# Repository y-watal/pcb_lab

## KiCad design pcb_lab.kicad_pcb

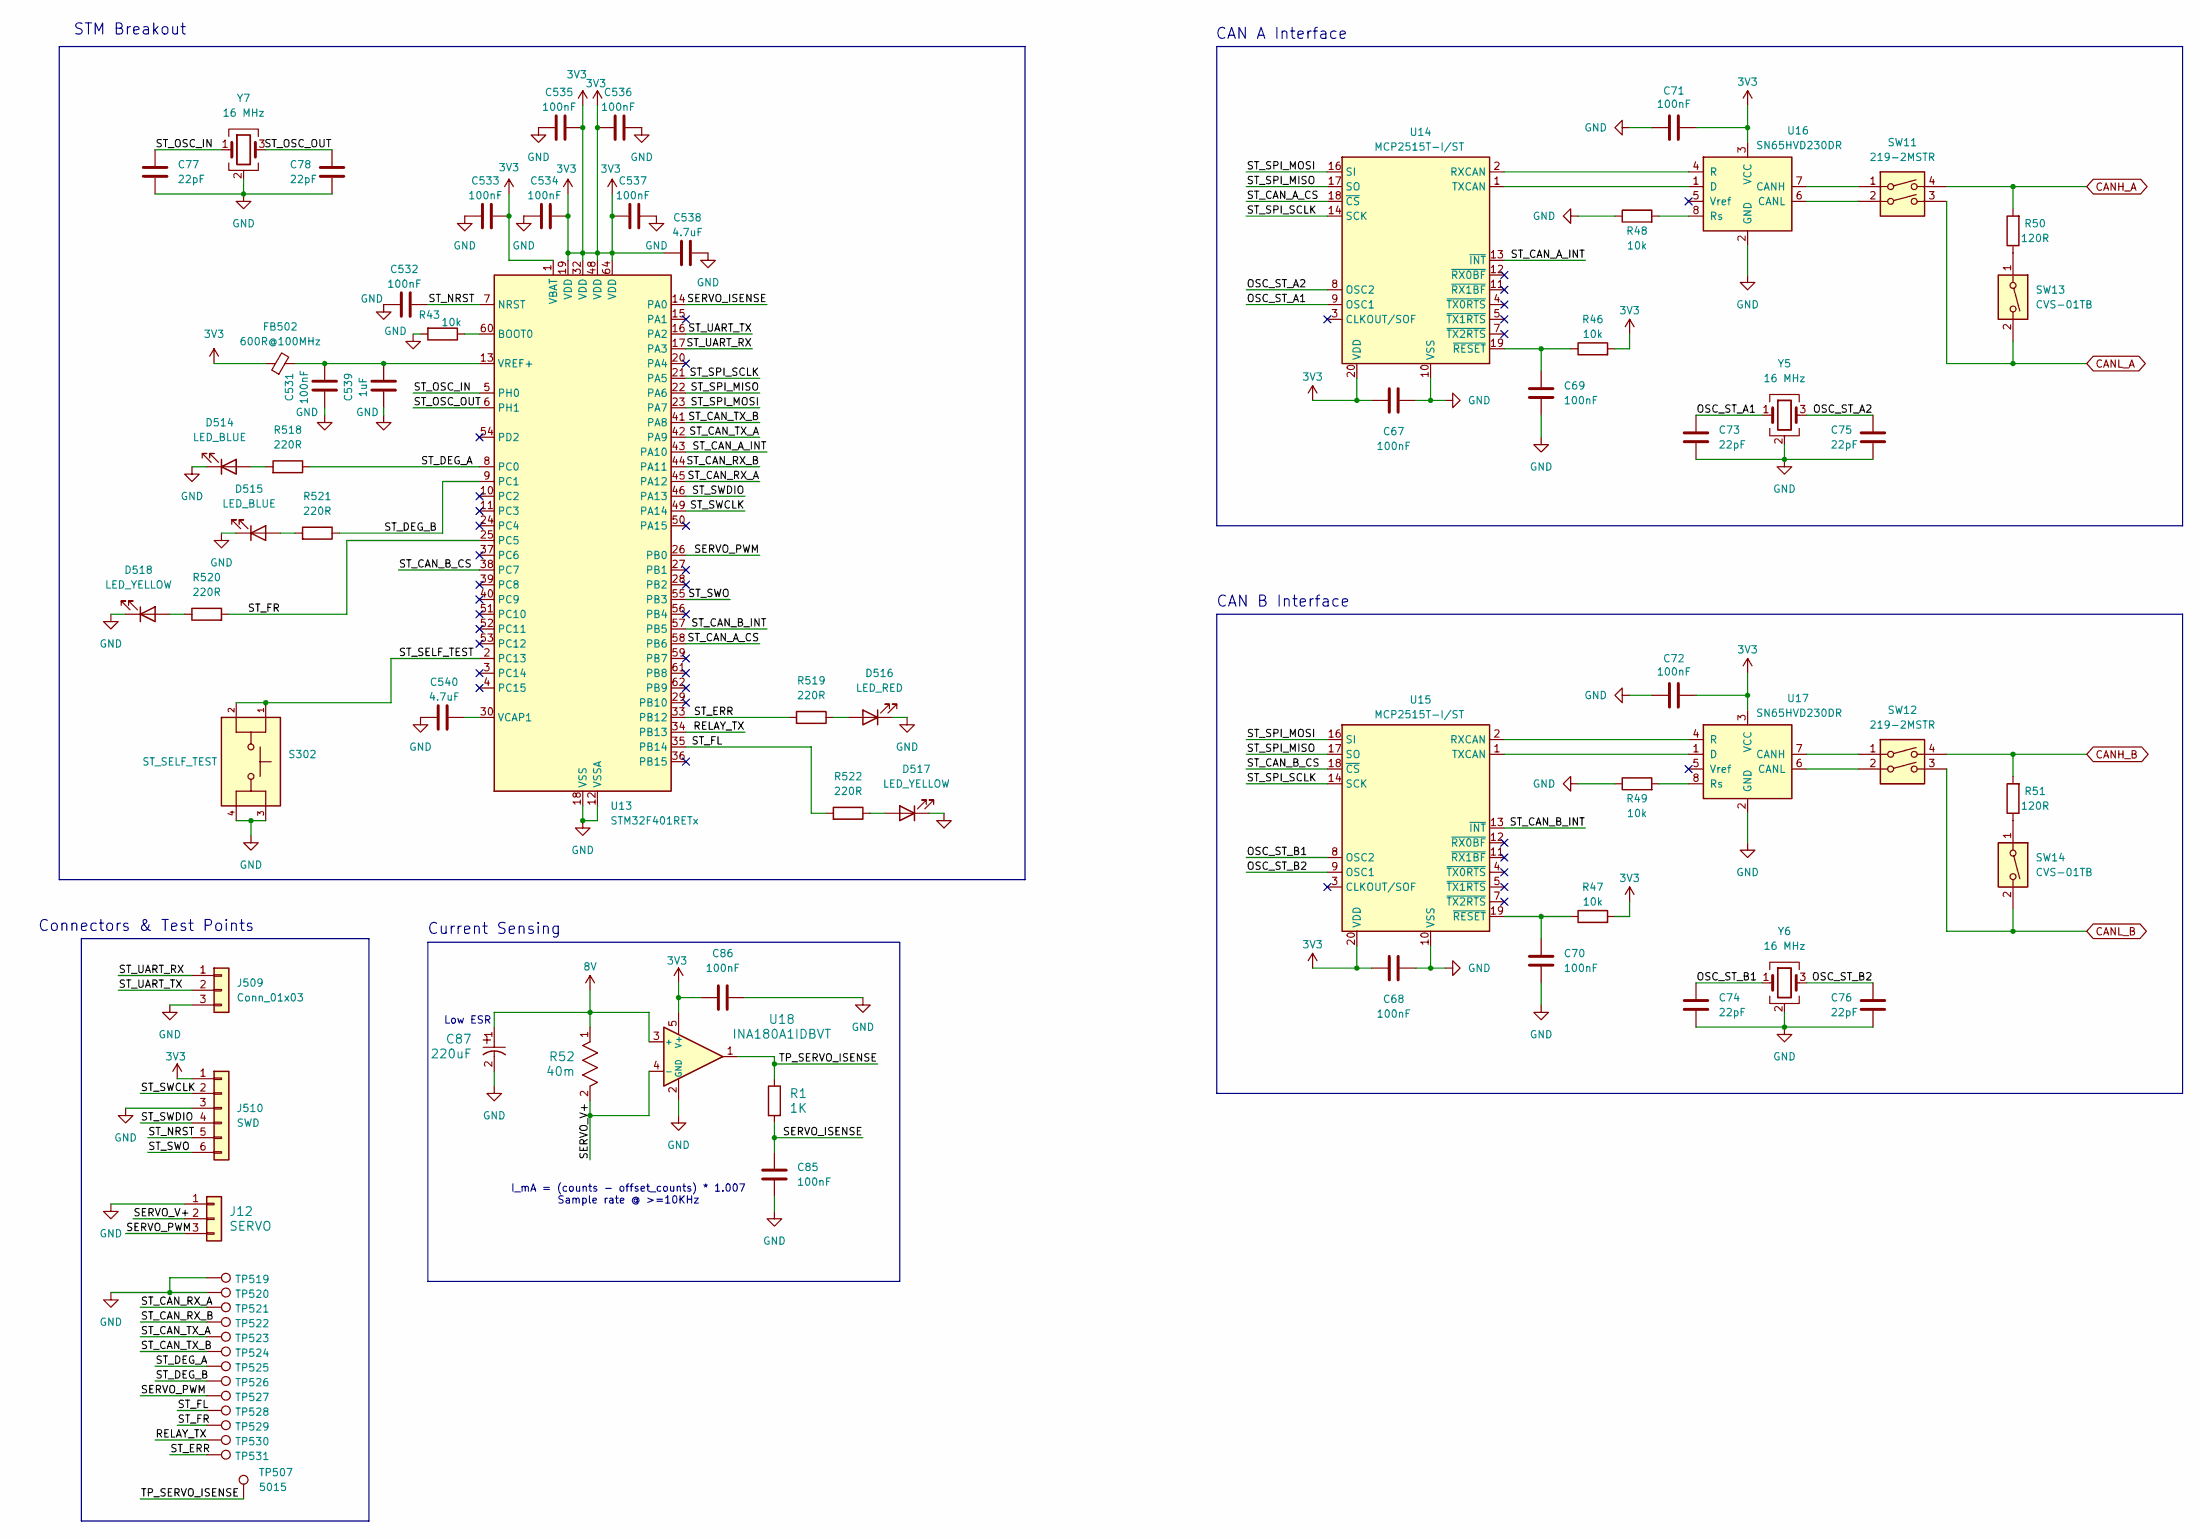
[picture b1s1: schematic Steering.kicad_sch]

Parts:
C67, C68, C69, C70, C71, C72, C85, C86, C531, C532, C533, C534, C535, C536, C537: 100nF; C_0603_1608Metric; Manufacturer Part Number C0603C104K3RACAUTO; LCSC Part # C172738
C73, C74, C75, C76, C77, C78: 22pF; C_0603_1608Metric; Manufacturer Part Number C0603C220J1GACTU; LCSC Part # C2168649
C87: 220uF; CAP_EEFK_E_PAN-M; Manufacturer Part Number EEEFK1C221P; LCSC Part # C178534
C538, C540: 4.7uF; C_0805_2012Metric; Manufacturer Part Number GRM219R61E475KA73D
C539: 1uF; C_0603_1608Metric; Manufacturer Part Number CL10A105KB8NNNC; LCSC Part # C15849
D514, D515: LED_BLUE; LED_D3.0mm; Manufacturer Part Number 151033BS03000
D516: LED_RED; LED_D3.0mm; Manufacturer Part Number 151031SS06000; LCSC Part # C6067185
D517, D518: LED_YELLOW; LED_D3.0mm; Manufacturer Part Number 151031YS06000
FB502: 600R@100MHz; L_0603_1608Metric; Manufacturer Part Number 742863160
J12: SERVO; CONN_55660330-SD_MOL; Manufacturer Part Number 39301039; LCSC Part # C505007
J509: Conn_01x03; PinHeader_1x03_P2.54mm_Vertical; Manufacturer Part Number TSW-103-07-G-S
J510: SWD; PinHeader_1x06_P2.54mm_Vertical; Manufacturer Part Number TSW-106-07-G-S
R1: 1K; RES_CRCW_0603-M; Manufacturer Part Number CRCW06031K00FKEA; LCSC Part # C844920
R43: 10k; R_0603_1608Metric
R46, R47, R48, R49: 10k; R_0603_1608Metric; Manufacturer Part Number CRCW060310K0FKEA; LCSC Part # C844918
R50, R51: 120R; R_0603_1608Metric; Manufacturer Part Number RC0603FR-07120RL; LCSC Part # C114640
R52: 40m; RES_2512_WSL-M; Manufacturer Part Number WSL2512R0400FEA; LCSC Part # C844291
R518, R519, R520, R521, R522: 220R; R_0603_1608Metric; Manufacturer Part Number CRCW0603220RFKEA; LCSC Part # C844757
S302: ST_SELF_TEST; SW_SWT0210-045026GSA_REVA; Manufacturer Part Number SWT0210-045026GSA
SW11, SW12: 219-2MSTR; SW_DIP_SPSTx02_Slide_6.7x6.64mm_W8.61mm_P2.54mm_LowProfile; Manufacturer Part Number 219-2MSTR; LCSC Part # C2961978
SW13, SW14: CVS-01TB; SW_DIP_SPSTx01_Slide_Copal_CVS-01xB_W5.9mm_P1mm; Manufacturer Part Number CVS-01TB; LCSC Part # C2921743
TP507, TP519, TP520, TP521, TP522, TP523, TP524, TP525, TP526, TP527, TP528, TP529, TP530, TP531: 5015; TestPoint_Keystone_5015_Micro_Mini; Manufacturer Part Number 5015; LCSC Part # C2906768
U13: STM32F401RETx; LQFP-64_10x10mm_P0.5mm
U14, U15: MCP2515T-I/ST; TSSOP-20_4.4x6.5mm_P0.65mm; Manufacturer Part Number MCP2515T-I/ST; LCSC Part # C185941
U16, U17: SN65HVD230DR; SOIC-8_3.9x4.9mm_P1.27mm; Manufacturer Part Number SN65HVD230DR; LCSC Part # C12084
U18: INA180A1IDBVT; DBV0005A_M; Manufacturer Part Number INA180A1IDBVT; LCSC Part # C2057273
Y5, Y6, Y7: 16 MHz; Crystal_SMD_3225-4Pin_3.2x2.5mm; Manufacturer Part Number CX3225SB16000H0FLJCC

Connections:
3V3: C67.1, C68.1, C71.1, C72.1, C86.1, C533.2, C534.2, C535.2, C536.1, C537.1, C538.1, FB502.1, J510.1, R46.2, R47.2, U13.1 (VBAT), U13.19 (VDD), U13.32 (VDD), U13.48 (VDD), U13.64 (VDD), U14.20 (VDD), U15.20 (VDD), U16.3 (VCC), U17.3 (VCC), U18.5 (V+); also elsewhere on the board
8V: C87.1, R52.1, U18.3 (+); also elsewhere on the board
/Steering/OSC_ST_A1: C73.1, U14.9 (OSC1), Y5.1
/Steering/OSC_ST_A2: C75.1, U14.8 (OSC2), Y5.3
/Steering/OSC_ST_B1: C74.1, U15.8 (OSC2), Y6.1
/Steering/OSC_ST_B2: C76.1, U15.9 (OSC1), Y6.3
/Steering/RELAY_TX: TP530.1 (1_1), U13.34 (PB13)
/Steering/SERVO_ISENSE: C85.1, R1.2, U13.14 (PA0)
/Steering/SERVO_PWM: J12.3, TP527.1 (1_1), U13.26 (PB0)
/Steering/SERVO_V+: J12.2, R52.2, U18.4 (-)
/Steering/ST_CAN_A_CS: U13.58 (PB6), U14.18 (~CS)
/Steering/ST_CAN_A_INT: U13.43 (PA10), U14.13 (~INT)
/Steering/ST_CAN_B_CS: U13.38 (PC7), U15.18 (~CS)
/Steering/ST_CAN_B_INT: U13.57 (PB5), U15.13 (~INT)
/Steering/ST_CAN_RX_A: TP521.1 (1_1), U13.45 (PA12)
/Steering/ST_CAN_RX_B: TP522.1 (1_1), U13.44 (PA11)
/Steering/ST_CAN_TX_A: TP523.1 (1_1), U13.42 (PA9)
/Steering/ST_CAN_TX_B: TP524.1 (1_1), U13.41 (PA8)
/Steering/ST_DEG_A: R518.1, TP525.1 (1_1), U13.8 (PC0)
/Steering/ST_DEG_B: R521.1, TP526.1 (1_1), U13.9 (PC1)
/Steering/ST_ERR: R519.2, TP531.1 (1_1), U13.33 (PB12)
/Steering/ST_FL: R522.2, TP528.1 (1_1), U13.35 (PB14)
/Steering/ST_FR: R520.2, TP529.1 (1_1), U13.25 (PC5)
/Steering/ST_NRST: C532.2, J510.5, U13.7 (NRST)
/Steering/ST_OSC_IN: C77.1, U13.5 (PH0), Y7.1
/Steering/ST_OSC_OUT: C78.1, U13.6 (PH1), Y7.3
/Steering/ST_SELF_TEST: S302.1, S302.2, U13.2 (PC13)
/Steering/ST_SPI_MISO: U13.22 (PA6), U14.17 (SO), U15.17 (SO)
/Steering/ST_SPI_MOSI: U13.23 (PA7), U14.16 (SI), U15.16 (SI)
/Steering/ST_SPI_SCLK: U13.21 (PA5), U14.14 (SCK), U15.14 (SCK)
/Steering/ST_SWCLK: J510.2, U13.49 (PA14)
/Steering/ST_SWDIO: J510.4, U13.46 (PA13)
/Steering/ST_SWO: J510.6, U13.55 (PB3)
/Steering/ST_UART_RX: J509.1, U13.17 (PA3)
/Steering/ST_UART_TX: J509.2, U13.16 (PA2)
/Steering/TP_SERVO_ISENSE: R1.1, TP507.1 (1_1), U18.1
CANH_A: R50.2, SW11.4; also elsewhere on the board
CANH_B: R51.2, SW12.4; also elsewhere on the board
CANL_A: SW11.3, SW13.2; also elsewhere on the board
CANL_B: SW12.3, SW14.2; also elsewhere on the board
GND: C67.2, C68.2, C69.2, C70.2, C71.2, C72.2, C73.2, C74.2, C75.2, C76.2, C77.2, C78.2, C85.2, C86.2, C87.2, C531.1, C532.1, C533.1, C534.1, C535.1, C536.2, C537.2, C538.2, C539.1, C540.1, D514.1 (K), D515.1 (K), D516.1 (K), D517.1 (K), D518.1 (K), J12.1, J509.3, J510.3, R43.2, R48.1, R49.1, S302.3, S302.4, TP519.1 (1_1), TP520.1 (1_1), U13.12 (VSSA), U13.18 (VSS), U13.31 (VSS), U13.47 (VSS), U13.63 (VSS), U14.10 (VSS), U15.10 (VSS), U16.2 (GND), U17.2 (GND), U18.2 (GND), Y5.2 (G), Y5.4 (G), Y6.2 (G), Y6.4 (G), Y7.2 (G), Y7.4 (G); also elsewhere on the board
unnamed: D514.2 (A), R518.2
unnamed: D515.2 (A), R521.2
unnamed: D516.2 (A), R519.1
unnamed: D517.2 (A), R522.1
unnamed: D518.2 (A), R520.1
unnamed: R50.1, SW13.1
unnamed: R51.1, SW14.1
unnamed: R43.1, U13.60 (BOOT0)
unnamed: C540.2, U13.30 (VCAP1)
unnamed: C531.2, C539.2, FB502.2, U13.13 (VREF+)
unnamed: U14.2 (RXCAN), U16.4 (R)
unnamed: U14.1 (TXCAN), U16.1 (D)
unnamed: C69.1, R46.1, U14.19 (~RESET)
unnamed: U15.2 (RXCAN), U17.4 (R)
unnamed: U15.1 (TXCAN), U17.1 (D)
unnamed: C70.1, R47.1, U15.19 (~RESET)
unnamed: SW11.1, U16.7 (CANH)
unnamed: SW11.2, U16.6 (CANL)
unnamed: R48.2, U16.8 (Rs)
unnamed: SW12.1, U17.7 (CANH)
unnamed: SW12.2, U17.6 (CANL)
unnamed: R49.2, U17.8 (Rs)

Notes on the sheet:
CAN B Interface
CAN A Interface
STM Breakout
Current Sensing
I_mA = (counts − offset_counts) * 1.007 Sample rate @ >=10KHz
Connectors & Test Points
Low ESR

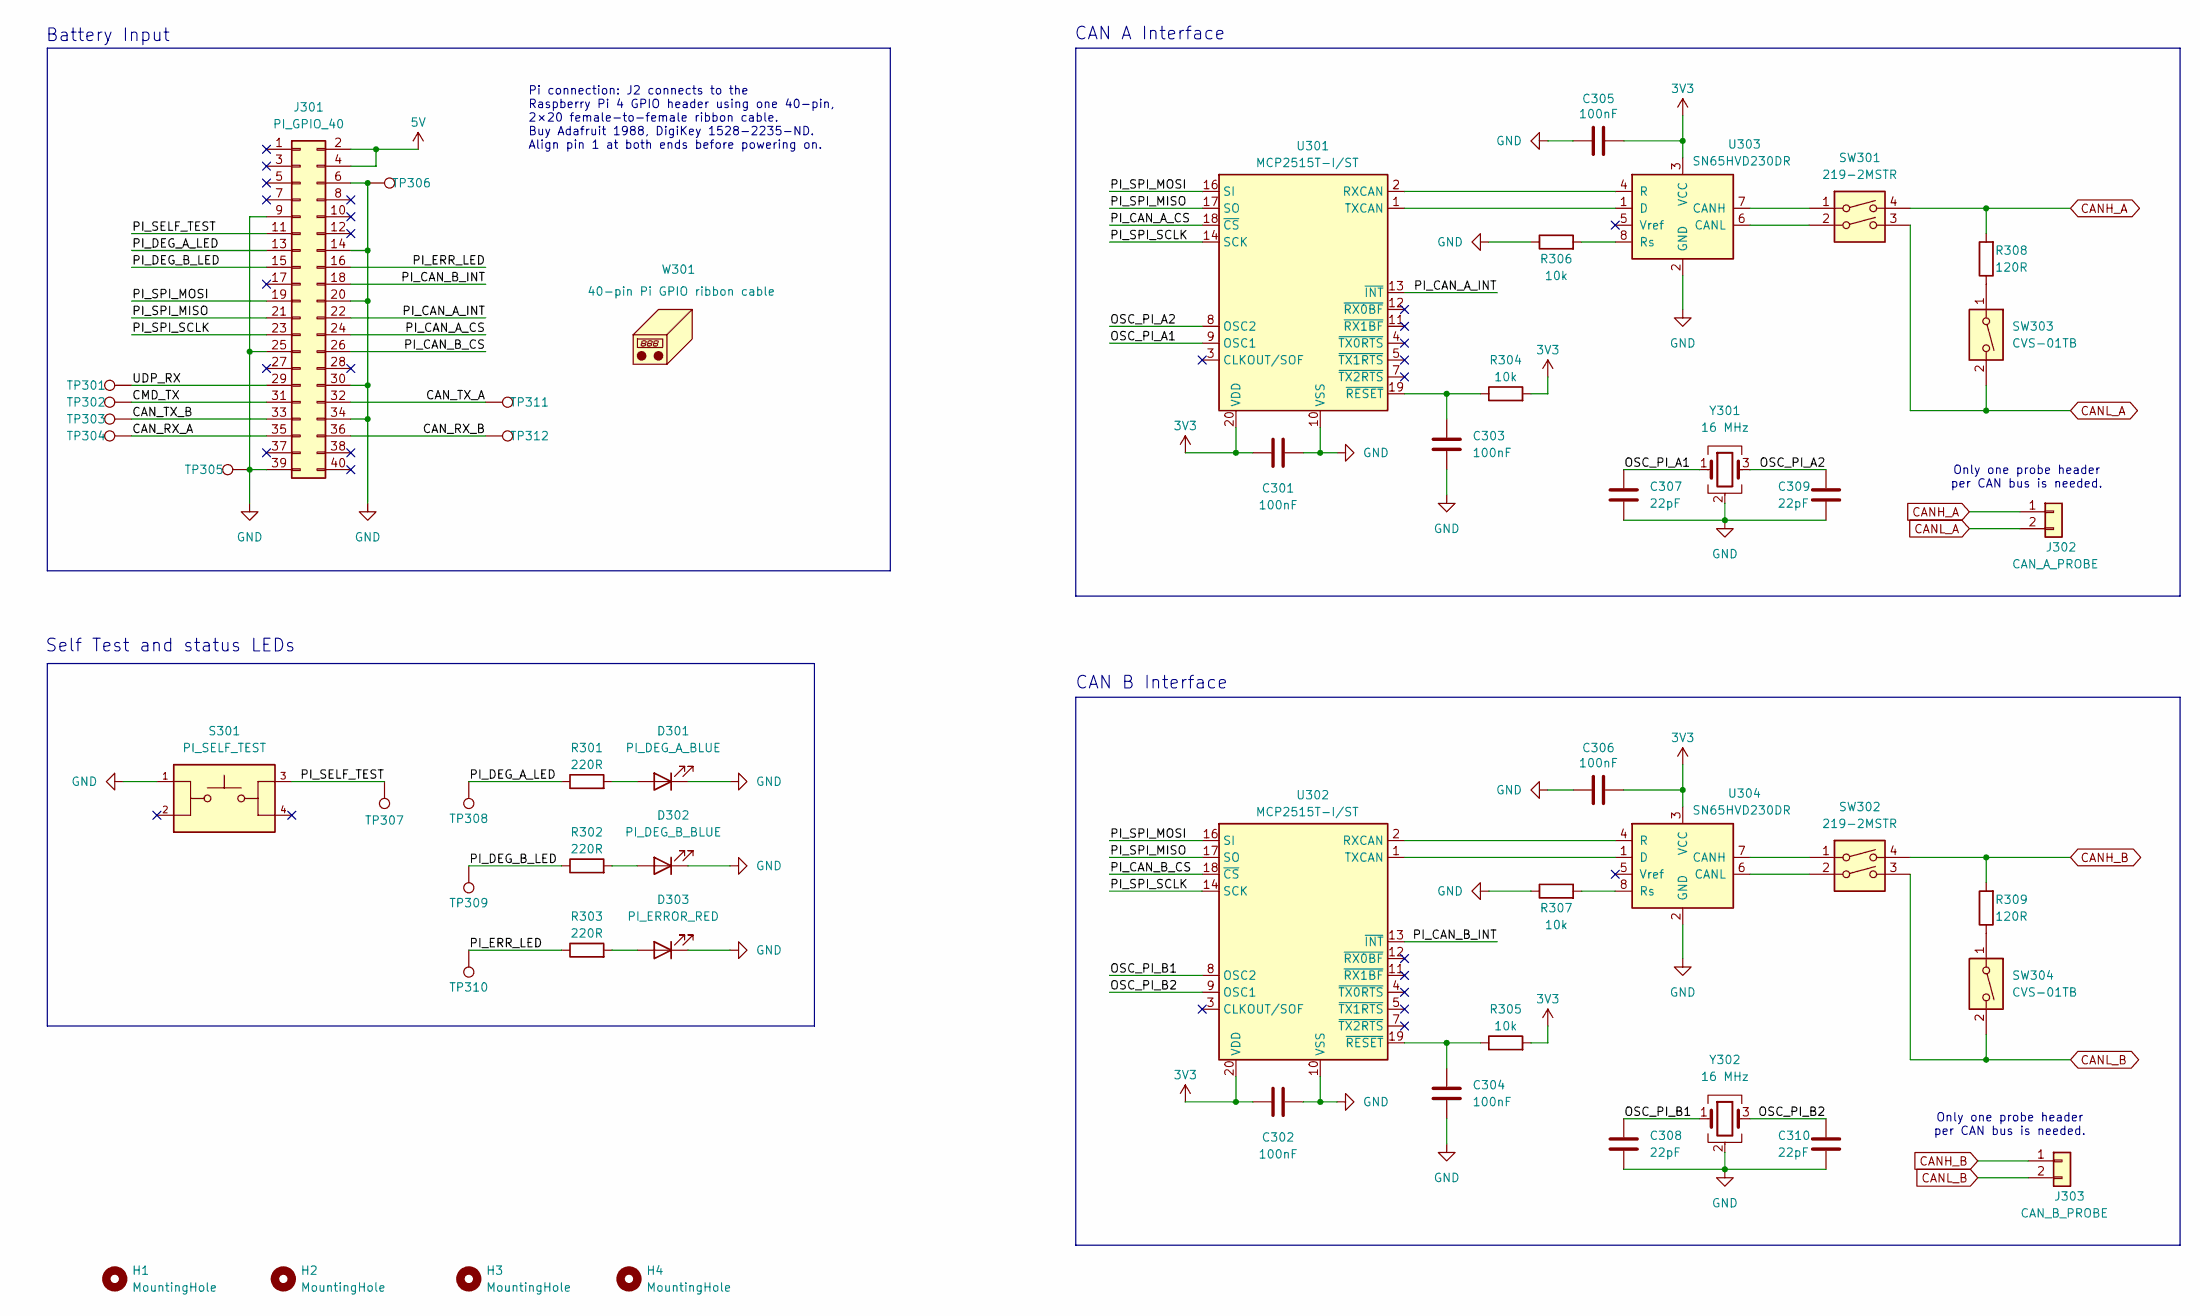
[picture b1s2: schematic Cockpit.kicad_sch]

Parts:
C301, C302, C303, C304, C305, C306: 100nF; C_0603_1608Metric; Manufacturer Part Number C0603C104K3RACAUTO; LCSC Part # C172738
C307, C308, C309, C310: 22pF; C_0603_1608Metric; Manufacturer Part Number C0603C220J1GACTU; LCSC Part # C2168649
D301: PI_DEG_A_BLUE; LED_D3.0mm; Manufacturer Part Number 151033BS03000
D302: PI_DEG_B_BLUE; LED_D3.0mm; Manufacturer Part Number 151033BS03000
D303: PI_ERROR_RED; LED_D3.0mm; Manufacturer Part Number 151031SS06000; LCSC Part # C6067185
H1, H2, H3, H4: MountingHole; MountingHole_3.2mm_M3
J301: PI_GPIO_40; PinHeader_2x20_P2.54mm_Vertical; Manufacturer Part Number TSW-120-07-G-D
J302: CAN_A_PROBE; PinHeader_1x02_P2.54mm_Vertical; Manufacturer Part Number TSW-102-07-G-S
J303: CAN_B_PROBE; PinHeader_1x02_P2.54mm_Vertical; Manufacturer Part Number TSW-102-07-G-S
R301, R302, R303: 220R; R_0603_1608Metric; Manufacturer Part Number CRCW0603220RFKEA; LCSC Part # C844757
R304, R305, R306, R307: 10k; R_0603_1608Metric; Manufacturer Part Number CRCW060310K0FKEA; LCSC Part # C844918
R308, R309: 120R; R_0603_1608Metric; Manufacturer Part Number RC0603FR-07120RL; LCSC Part # C114640
S301: PI_SELF_TEST; SW_SWT0210-045026GSA_REVA; Manufacturer Part Number SWT0210-045026GSA
SW301, SW302: 219-2MSTR; SW_DIP_SPSTx02_Slide_6.7x6.64mm_W8.61mm_P2.54mm_LowProfile; Manufacturer Part Number 219-2MSTR; LCSC Part # C2961978
SW303, SW304: CVS-01TB; SW_DIP_SPSTx01_Slide_Copal_CVS-01xB_W5.9mm_P1mm; Manufacturer Part Number CVS-01TB; LCSC Part # C2921743
TP301, TP302, TP303, TP304, TP305, TP306, TP307, TP308, TP309, TP310, TP311, TP312: 5015; TestPoint_Keystone_5015_Micro_Mini; Manufacturer Part Number 5015; LCSC Part # C2906768
U301, U302: MCP2515T-I/ST; TSSOP-20_4.4x6.5mm_P0.65mm; Manufacturer Part Number MCP2515T-I/ST; LCSC Part # C185941
U303, U304: SN65HVD230DR; SOIC-8_3.9x4.9mm_P1.27mm; Manufacturer Part Number SN65HVD230DR; LCSC Part # C12084
W301: 40-pin Pi GPIO ribbon cable; Manufacturer Part Number 1988; DigiKey Part # 1528-2235-ND
Y301, Y302: 16 MHz; Crystal_SMD_3225-4Pin_3.2x2.5mm; Manufacturer Part Number CX3225SB16000H0FLJCC

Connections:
3V3: C301.1, C302.1, C305.1, C306.1, R304.2, R305.2, U301.20 (VDD), U302.20 (VDD), U303.3 (VCC), U304.3 (VCC); also elsewhere on the board
5V: J301.2, J301.4; also elsewhere on the board
/Cockpit/CAN_RX_A: J301.35, TP304.1 (1_1)
/Cockpit/CAN_RX_B: J301.36, TP312.1 (1_1)
/Cockpit/CAN_TX_A: J301.32, TP311.1 (1_1)
/Cockpit/CAN_TX_B: J301.33, TP303.1 (1_1)
/Cockpit/CMD_TX: J301.31, TP302.1 (1_1)
/Cockpit/OSC_PI_A1: C307.1, U301.9 (OSC1), Y301.1
/Cockpit/OSC_PI_A2: C309.1, U301.8 (OSC2), Y301.3
/Cockpit/OSC_PI_B1: C308.1, U302.8 (OSC2), Y302.1
/Cockpit/OSC_PI_B2: C310.1, U302.9 (OSC1), Y302.3
/Cockpit/PI_CAN_A_CS: J301.24, U301.18 (~CS)
/Cockpit/PI_CAN_A_INT: J301.22, U301.13 (~INT)
/Cockpit/PI_CAN_B_CS: J301.26, U302.18 (~CS)
/Cockpit/PI_CAN_B_INT: J301.18, U302.13 (~INT)
/Cockpit/PI_DEG_A_LED: J301.13, R301.1, TP308.1 (1_1)
/Cockpit/PI_DEG_B_LED: J301.15, R302.1, TP309.1 (1_1)
/Cockpit/PI_ERR_LED: J301.16, R303.1, TP310.1 (1_1)
/Cockpit/PI_SELF_TEST: J301.11, S301.3, TP307.1 (1_1)
/Cockpit/PI_SPI_MISO: J301.21, U301.17 (SO), U302.17 (SO)
/Cockpit/PI_SPI_MOSI: J301.19, U301.16 (SI), U302.16 (SI)
/Cockpit/PI_SPI_SCLK: J301.23, U301.14 (SCK), U302.14 (SCK)
/Cockpit/UDP_RX: J301.29, TP301.1 (1_1)
CANH_A: J302.1, R308.2, SW301.4; also elsewhere on the board
CANH_B: J303.1, R309.2, SW302.4; also elsewhere on the board
CANL_A: J302.2, SW301.3, SW303.2; also elsewhere on the board
CANL_B: J303.2, SW302.3, SW304.2; also elsewhere on the board
GND: C301.2, C302.2, C303.2, C304.2, C305.2, C306.2, C307.2, C308.2, C309.2, C310.2, D301.1 (K), D302.1 (K), D303.1 (K), J301.6, J301.9, J301.14, J301.20, J301.25, J301.30, J301.34, J301.39, R306.1, R307.1, S301.1, TP305.1 (1_1), TP306.1 (1_1), U301.10 (VSS), U302.10 (VSS), U303.2 (GND), U304.2 (GND), Y301.2 (G), Y301.4 (G), Y302.2 (G), Y302.4 (G); also elsewhere on the board
unnamed: D301.2 (A), R301.2
unnamed: D302.2 (A), R302.2
unnamed: D303.2 (A), R303.2
unnamed: R308.1, SW303.1
unnamed: R309.1, SW304.1
unnamed: U301.2 (RXCAN), U303.4 (R)
unnamed: U301.1 (TXCAN), U303.1 (D)
unnamed: C303.1, R304.1, U301.19 (~RESET)
unnamed: U302.2 (RXCAN), U304.4 (R)
unnamed: U302.1 (TXCAN), U304.1 (D)
unnamed: C304.1, R305.1, U302.19 (~RESET)
unnamed: SW301.1, U303.7 (CANH)
unnamed: SW301.2, U303.6 (CANL)
unnamed: R306.2, U303.8 (Rs)
unnamed: SW302.1, U304.7 (CANH)
unnamed: SW302.2, U304.6 (CANL)
unnamed: R307.2, U304.8 (Rs)

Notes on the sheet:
Pi connection: J2 connects to the Raspberry Pi 4 GPIO header using one 40-pin, 2×20 female-to-female ribbon cable. Buy Adafruit 1988, DigiKey 1528-2235-ND. Align pin 1 at both ends before powering on.
Only one probe header per CAN bus is needed.
CAN A Interface
CAN B Interface
Self Test and status LEDs
Battery Input

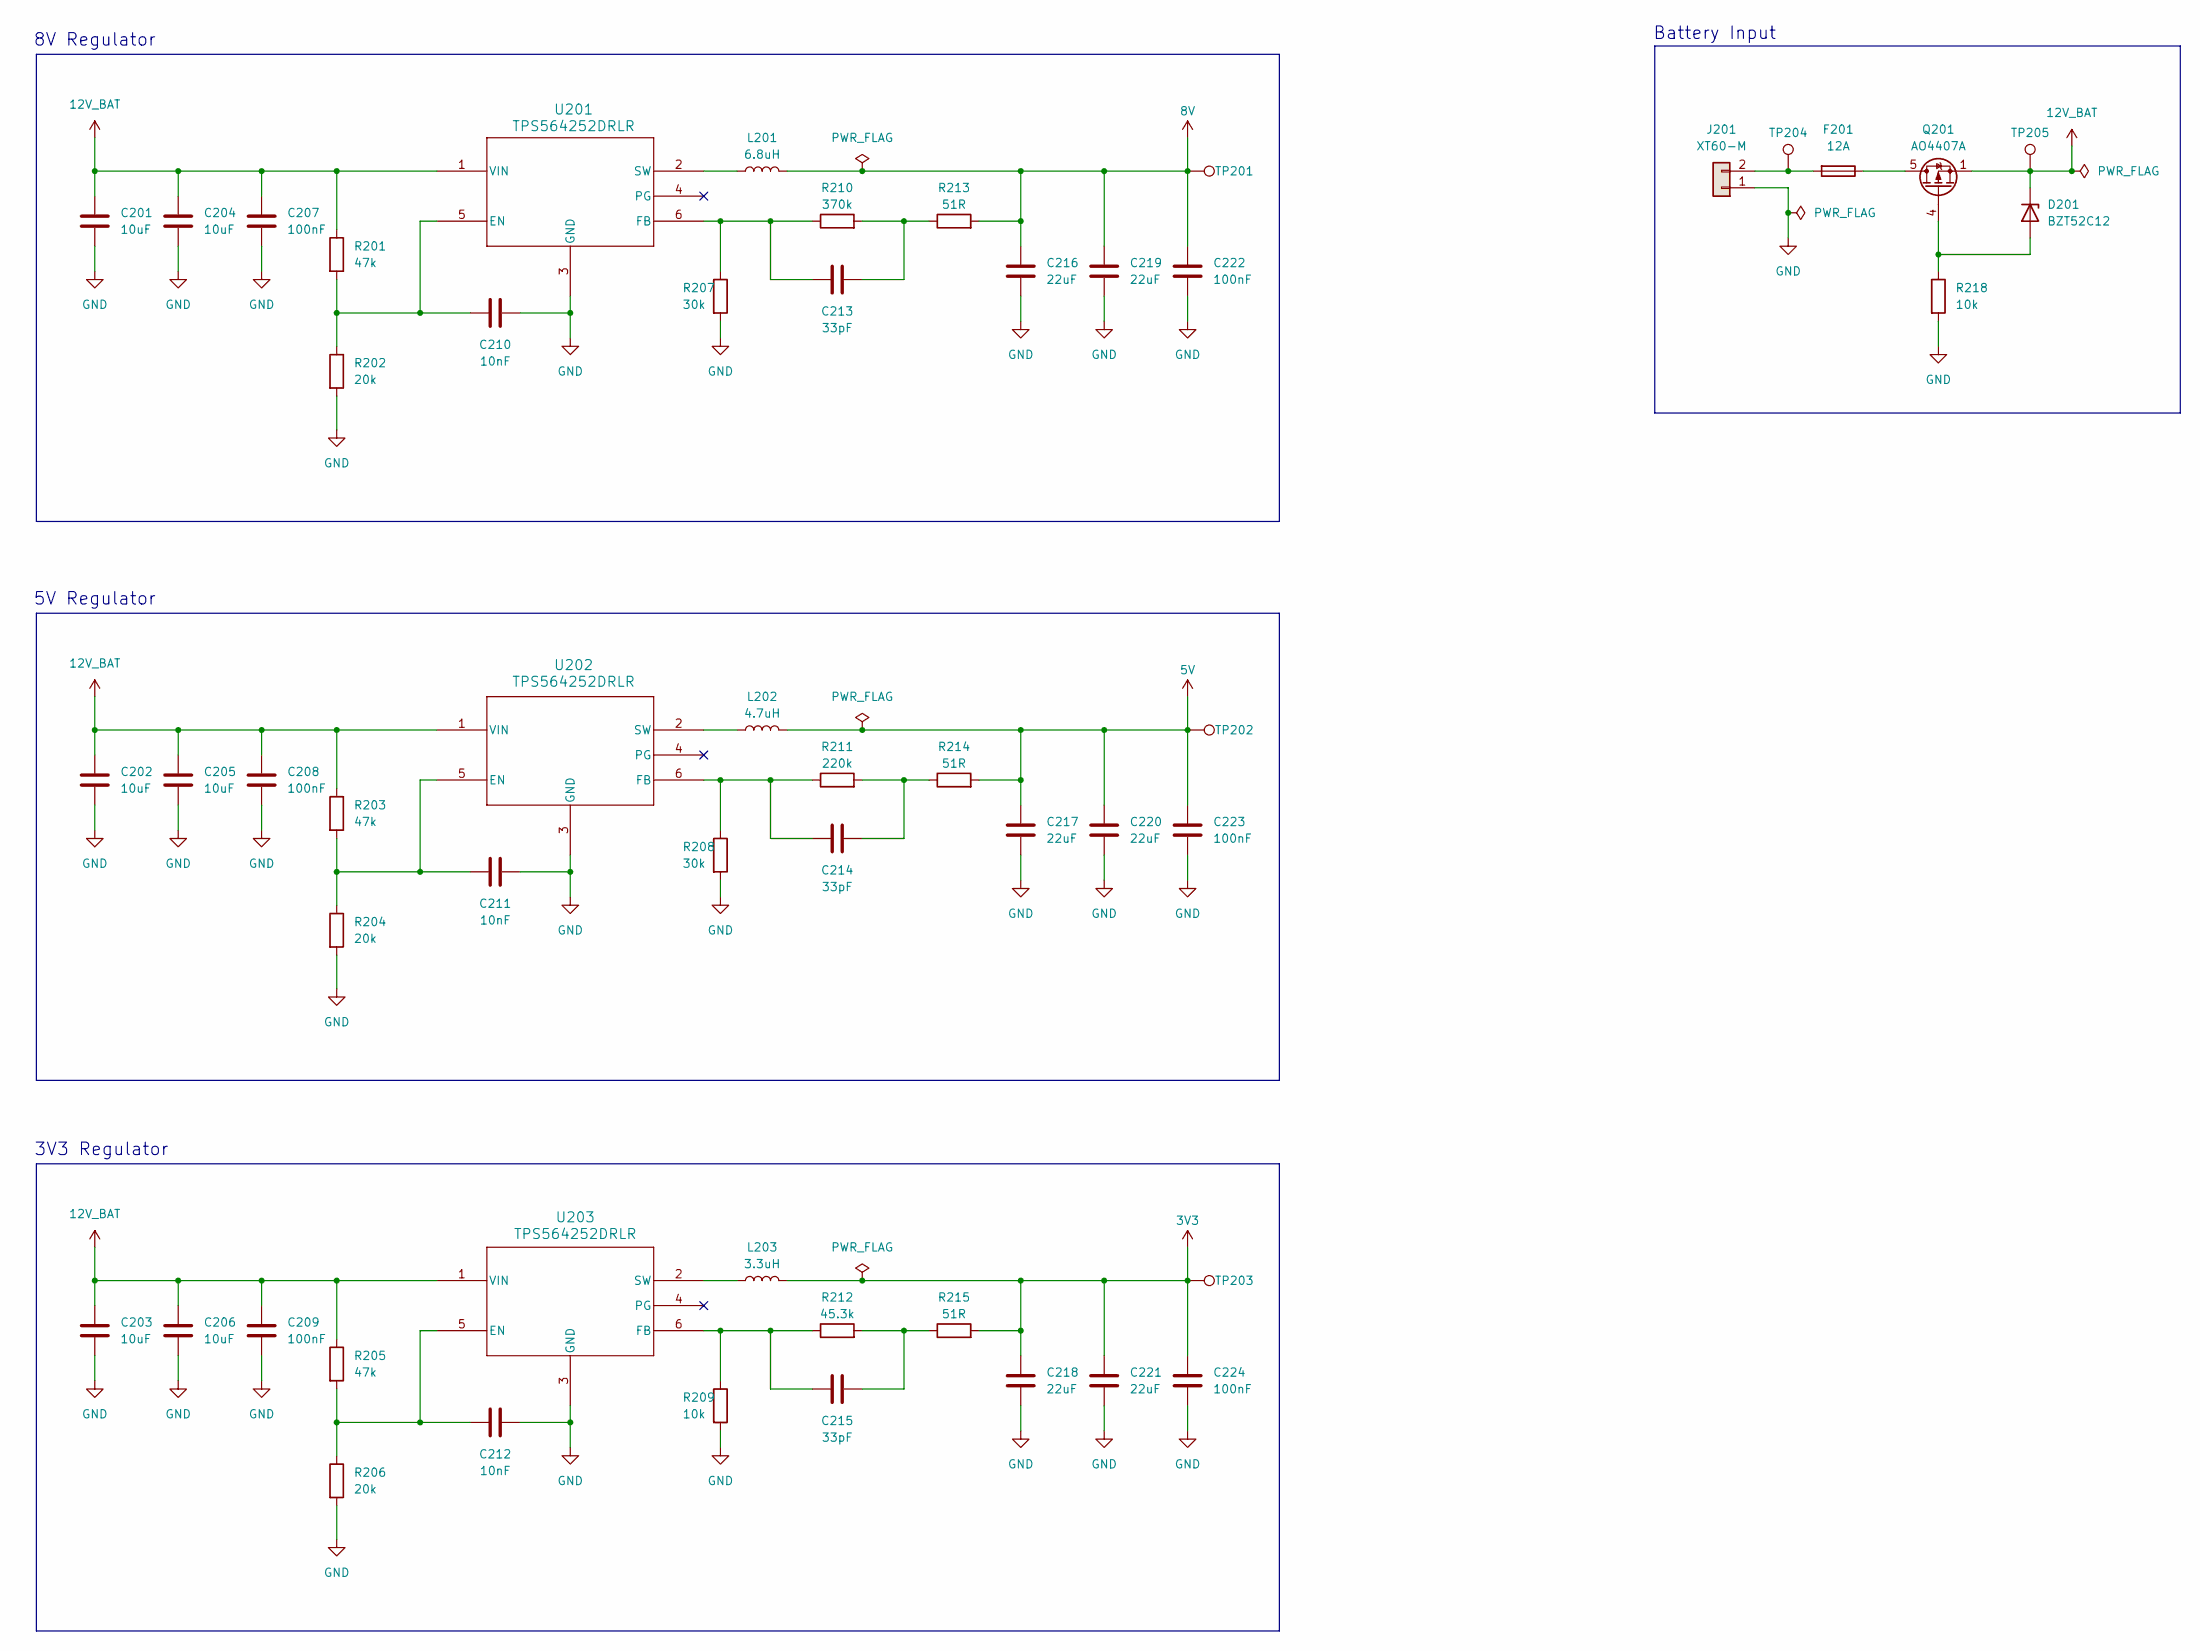
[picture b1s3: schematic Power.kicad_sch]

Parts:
C201, C202, C203, C204, C205, C206: 10uF; C_0805_2012Metric; Manufacturer Part Number C0805C106M3PACTU
C207, C208, C209, C222, C223, C224: 100nF; C_0603_1608Metric; Manufacturer Part Number C0603C104K3RACAUTO; LCSC Part # C172738
C210, C211, C212: 10nF; C_0603_1608Metric; Manufacturer Part Number CL10B103KB8NNNC; LCSC Part # C1589
C213, C214, C215: 33pF; C_0603_1608Metric; Manufacturer Part Number CL10C330JB8NNNC; LCSC Part # C1663
C216, C217, C218, C219, C220, C221: 22uF; C_1206_3216Metric; Manufacturer Part Number 12063D226KAT2A; LCSC Part # C2167862
D201: BZT52C12; D_SOD-123; Manufacturer Part Number BZT52C12; LCSC Part # C271259
F201: 12A; Fuse_Littelfuse-NANO2-451_453; Manufacturer Part Number 0451012.MRL; LCSC Part # C99549
J201: XT60-M; AMASS_XT60-M_1x02_P7.20mm_Vertical; Manufacturer Part Number XT60-M; LCSC Part # C98733
L201: 6.8uH; Inductor_Bourns-SRR1280; Manufacturer Part Number SRR1280-6R8Y; LCSC Part # C6824606
L202: 4.7uH; L_Bourns_SRP5030T; Manufacturer Part Number SRP5030TA-4R7M; LCSC Part # C2047088
L203: 3.3uH; L_Bourns_SRP5030T; Manufacturer Part Number SRP5030TA-3R3M; LCSC Part # C2042118
Q201: AO4407A; SOIC-8_3.9x4.9mm_P1.27mm; Manufacturer Part Number AO4407A; LCSC Part # C16072
R201, R203, R205: 47k; R_0603_1608Metric; Manufacturer Part Number RC0603FR-0747KL; LCSC Part # C105579
R202, R204, R206: 20k; R_0603_1608Metric; Manufacturer Part Number RC0603FR-0720KL; LCSC Part # C105575
R207, R208: 30k; R_0603_1608Metric; Manufacturer Part Number RC0603FR-0730KL; LCSC Part # C100001
R209, R218: 10k; R_0603_1608Metric; Manufacturer Part Number CRCW060310K0FKEA; LCSC Part # C844918
R210: 370k; R_0603_1608Metric; Manufacturer Part Number RN73H1JTTD3703F100; LCSC Part # C4312636
R211: 220k; R_0603_1608Metric; Manufacturer Part Number CRCW0603220KFKEA; LCSC Part # C844756
R212: 45.3k; R_0603_1608Metric; Manufacturer Part Number CPF0603F45K3C1; LCSC Part # C2094769
R213, R214, R215: 51R; R_0603_1608Metric; Manufacturer Part Number RC0603FR-0751RL; LCSC Part # C114628
TP201, TP202, TP203, TP204, TP205: 5015; TestPoint_Keystone_5015_Micro_Mini; Manufacturer Part Number 5015; LCSC Part # C2906768
U201, U202, U203: TPS564252DRLR; SOT6_DRL_TEX-M; Manufacturer Part Number TPS564252DRLR; LCSC Part # C19191267

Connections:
3V3: C218.1, C221.1, C224.1, L203.2, R215.2, TP203.1 (1_1); also elsewhere on the board
5V: C217.1, C220.1, C223.1, L202.2, R214.2, TP202.1 (1_1); also elsewhere on the board
8V: C216.1, C219.1, C222.1, L201.2, R213.2, TP201.1 (1_1); also elsewhere on the board
12V_BAT: C201.1, C202.1, C203.1, C204.1, C205.1, C206.1, C207.1, C208.1, C209.1, D201.1 (K), Q201.1 (S), Q201.2 (S), Q201.3 (S), R201.1, R203.1, R205.1, TP205.1 (1_1), U201.1 (VIN), U202.1 (VIN), U203.1 (VIN); also elsewhere on the board
GND: C201.2, C202.2, C203.2, C204.2, C205.2, C206.2, C207.2, C208.2, C209.2, C210.2, C211.2, C212.2, C216.2, C217.2, C218.2, C219.2, C220.2, C221.2, C222.2, C223.2, C224.2, J201.1, R202.2, R204.2, R206.2, R207.2, R208.2, R209.2, R218.2, U201.3 (GND), U202.3 (GND), U203.3 (GND); also elsewhere on the board
unnamed: C213.2, R210.2, R213.1
unnamed: C214.2, R211.2, R214.1
unnamed: C215.2, R212.2, R215.1
unnamed: D201.2 (A), Q201.4 (G), R218.1
unnamed: F201.1, Q201.5 (D), Q201.6 (D), Q201.7 (D), Q201.8 (D)
unnamed: F201.2, J201.2, TP204.1 (1_1)
unnamed: C210.1, R201.2, R202.1, U201.5 (EN)
unnamed: C213.1, R207.1, R210.1, U201.6 (FB)
unnamed: L201.1, U201.2 (SW)
unnamed: C211.1, R203.2, R204.1, U202.5 (EN)
unnamed: C214.1, R208.1, R211.1, U202.6 (FB)
unnamed: L202.1, U202.2 (SW)
unnamed: C212.1, R205.2, R206.1, U203.5 (EN)
unnamed: C215.1, R209.1, R212.1, U203.6 (FB)
unnamed: L203.1, U203.2 (SW)

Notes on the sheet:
5V Regulator
3V3 Regulator
8V Regulator
Battery Input
